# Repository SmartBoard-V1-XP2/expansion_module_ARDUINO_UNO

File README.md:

# Expansion Module: Arduino UNO

## Overview
This repository hosts the design and implementation of an expansion module that is fully compatible with Arduino UNO, utilizing a single smartboard connector. This module is specifically designed to facilitate and enhance working with FPGA systems within the smartboard ecosystem. It allows for UART connection to FPGA circuits, and I2C communication with the smartboard's socket bus, enabling easy programming and configuration of other modules requiring I2C setup. Additionally, it supports sending and receiving interrupts to/from the FPGA, streamlining high-level debugging and simplifying hardware project control loaded onto the FPGA matrix.

The module's integration with Arduino's simplicity allows for the rapid addition of software functions for debugging or configuring hardware components, such as cameras, making it an invaluable tool for accelerating and improving work with FPGA systems on smartboards. It offers an efficient way to implement high-level debugging and straightforward project control over the hardware setup.

The module is programmed via a USB port, ensuring easy and accessible firmware updates and configurations. Users are reminded to load the Arduino firmware into the module upon assembly for booting, communication, and programming purposes.

## ATmega32u4 Microcontroller

The core of this expansion module is the ATmega32u4 microcontroller, which brings the advantage of having built-in USB communication, eliminating the need for an external USB-to-serial converter. This microcontroller operates at a frequency of 16 MHz and is equipped with 32KB of flash memory, 2.5KB of SRAM, and 1KB of EEPROM. Its integrated USB functionality not only simplifies programming and communication but also enables the module to act as a USB device itself, such as a mouse, keyboard, or other HID device, opening up a plethora of possibilities for embedded projects.

Key features of the ATmega32u4 include:
- Native USB support, facilitating direct programming and communication without additional hardware.
- 23 general-purpose input/output pins (GPIO), including PWM, analog inputs, and support for I2C and SPI communication.
- Built-in hardware support for serial communication via USART, making it ideal for projects that require communication with other microcontrollers or devices.

This microcontroller's versatility and comprehensive feature set make it an excellent choice for developers looking to leverage Arduino UNO compatibility with enhanced connectivity and processing capability.

For more detailed information on the ATmega32u4 microcontroller, including technical specifications and usage guidelines, please refer to the [ATmega32u4 Datasheet](ATmega16U4-32U4-DTE.pdf) available in this repository.

## Arduino UNO Software Compatibility

This expansion module harnesses the ATmega32u4 microcontroller, ensuring software compatibility with the Arduino UNO environment. While the physical layout of the module differs from standard Arduino UNO boards, making it incompatible with Arduino shields, it retains software compatibility. This means all the digital and analog pins, UART interfaces, and other peripherals like buttons and LEDs are mapped in accordance with the Arduino UNO's configuration, facilitating seamless integration with Arduino sketches and libraries.

The module's design prioritizes integration with smartboard systems while maintaining the ease of programming and versatility associated with the Arduino software environment. Developers can utilize the familiar Arduino IDE for programming the module, taking advantage of the vast collection of libraries and tools available within the Arduino ecosystem to expedite development and prototyping processes.

Key aspects of Arduino UNO software compatibility include:
- Use of the Arduino IDE for programming, which supports direct USB programming of the ATmega32u4 without the need for an external programmer.
- Alignment with Arduino UNO's pin mapping and functionality, ensuring that existing Arduino code and libraries can be used without modification.
- Support for Arduino's standard communication protocols, allowing the module to interface with other devices and modules through UART and I2C, as well as handle interrupts, in a manner consistent with Arduino UNO projects.

This approach allows the module to blend the robust hardware capabilities of the ATmega32u4 with the user-friendly software environment of Arduino, making it ideal for a wide range of applications from educational projects to complex IoT devices.

Developers are encouraged to install the Arduino bootloader and utilize the Arduino IDE for an optimal programming experience, leveraging the compatibility to streamline development and enhance the module's functionality within the smartboard ecosystem.

## Design Documentation

Below are images showcasing various aspects of the expansion module, providing a visual overview of its design, layout, and integration capabilities:

- **Schematic Overview**
  
  This image presents the schematic diagram of the expansion module, detailing the electrical connections and components.

- **Board Design**
  
  Here is the physical layout of the PCB, showing the placement of components and the overall design of the board.

- **Module Size and Dimensions**
  
  This picture illustrates the module's dimensions and size, providing a clear view of its compactness and how it fits within a smartboard system.

- **Integration with Smartboard and Arduino UNO**
  
  A visual representation of how the module integrates with a smartboard, including an example setup featuring an Arduino UNO.

- **Smartboard System Example**
  
  An example of a smartboard system fully equipped with several expansion modules, demonstrating the modular nature and versatility of the smartboard ecosystem.

These images collectively offer a comprehensive view of the expansion module's design, functionality, and integration potential within smartboard projects.

## Contributions and Feedback
Contributions to this project are welcome. If you have suggestions for improvement or have developed additional features, please fork the repository, make your changes, and submit a pull request. For any questions or issues, please open an issue in the GitHub repository.

## License
This project is licensed under the MIT License with the following terms:

- **Permission to Use**: You are free to use, modify, and distribute this design in both private and commercial settings.
- **Attribution Requirement**: While not required, attribution to the original author, Adam Łuczak, is appreciated. This can be done through a citation or a link back to this repository.
- **No Warranty**: This design is provided "as is", without warranty of any kind. Use it at your own risk.
- **Liability**: The author is not liable for any damages or losses that may arise from the use of this design.

For the full terms and conditions, please refer to the MIT License documentation.

## Contact
Should you have any inquiries or suggestions regarding this project, please don't hesitate to contact Adam Łuczak at adam.luczak@outlook.com.

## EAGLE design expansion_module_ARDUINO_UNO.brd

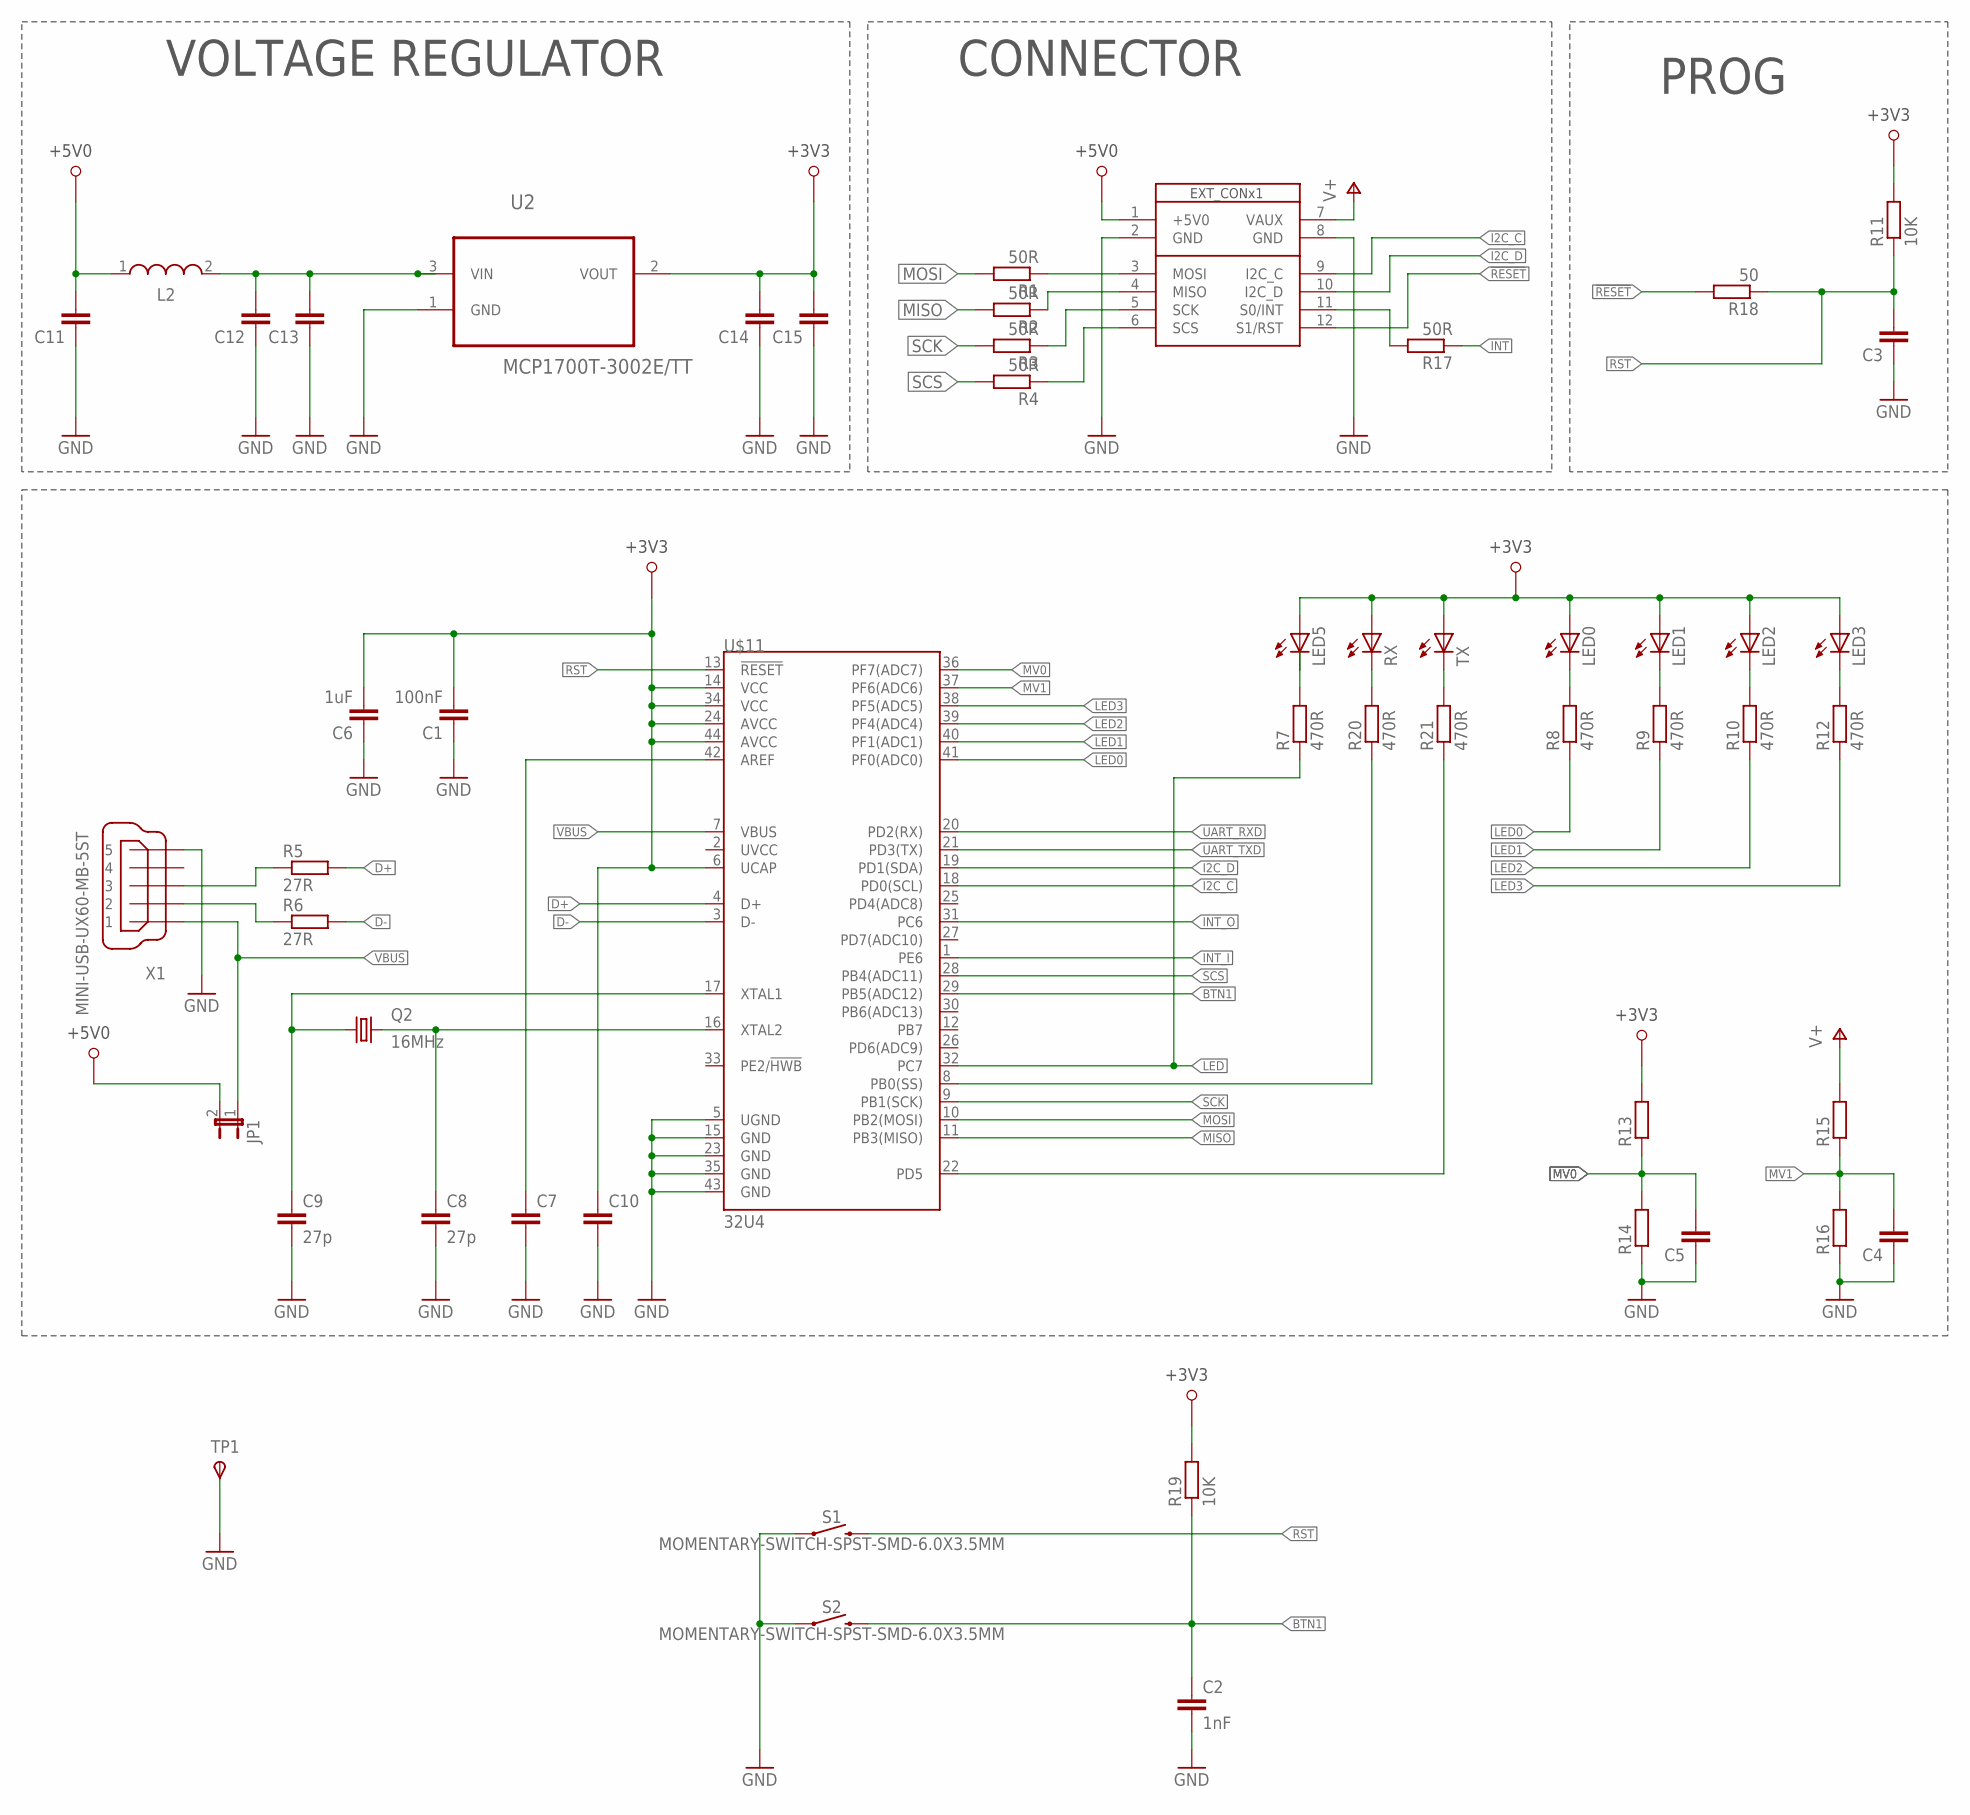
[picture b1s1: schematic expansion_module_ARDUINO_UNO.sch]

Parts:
C1: 100nF; C0603
C2: 1nF; C0603K
C3, C4, C5, C11, C12, C13, C14, C15: C-EUC0603; C0603
C6: 1uF; C0603
C7, C10: C-EUC0603K; C0603K
C8, C9: 27p; C0603K
JP1: JP1E; JP1
L2: WE-LQ_1210; WE-LQ_M
LED0, LED1, LED2, LED3, LED5: LED_ESML0603; LED_SML0603
Q2: 16MHz; 5.0X3.2_KX-9A
R1, R2, R3, R4, R17: 50R; R0603
R5, R6: 27R; R0603
R7, R8, R9, R10, R12, R20, R21: 470R; R0603
R11, R19: 10K; R0603
R13, R14, R15, R16: R-EU_R0603; R0603
R18: 50; R0603
RX: LED_ESML0603; LED_SML0603
S1, S2: MOMENTARY-SWITCH-SPST-SMD-6.0X3.5MM; TACTILE_SWITCH_SMD_6.0X3.5MM
TP1: TPSPAD1-13; P1-13
TX: LED_ESML0603; LED_SML0603
U2: MCP1700T-3002E/TT; SOT95P237X112-3N
U$1: SB_EXT_CON_X1_SPI; SB_EXT_CON_X1_FULL
U$11: 32U4; TQFP44
X1: MINI-USB-UX60-MB-5ST; UX60-MB-5ST

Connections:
!RESET: R18.2, U$1.12 (S1/RST)
+3V3: C1.2, C6.2, C10.1, C14.2, C15.2, LED0.A, LED1.A, LED2.A, LED3.A, LED5.A, R11.2, R13.2, R19.2, RX.A, TX.A, U2.2 (VOUT), U$11.6 (UCAP), U$11.14 (VCC), U$11.24 (AVCC), U$11.34 (VCC), U$11.44 (AVCC)
+5V0: C11.2, JP1.2, L2.1, U$1.1 (+5V0)
BTN1: C2.1, R19.1, S2.2, U$11.29 (PB5(ADC12))
D+: R5.2, U$11.4 (D+)
D-: R6.2, U$11.3 (D-)
GND: C1.1, C2.2, C3.1, C4.1, C5.1, C6.1, C7.2, C8.2, C9.2, C10.2, C11.1, C12.1, C13.1, C14.1, C15.1, R14.1, R16.1, S1.1, S2.1, TP1.TP, U2.1 (GND), U$1.2 (GND), U$1.8 (GND), U$11.5 (UGND), U$11.15 (GND), U$11.23 (GND), U$11.35 (GND), U$11.43 (GND), X1.5
I2C_C: U$1.9 (I2C_C), U$11.18 (PD0(SCL))
I2C_D: U$1.10 (I2C_D), U$11.19 (PD1(SDA))
INT: R17.1
INT_I: U$11.1 (PE6)
INT_O: U$11.31 (PC6)
LED: R7.1, U$11.32 (PC7)
LED0: R8.1, U$11.41 (PF0(ADC0))
LED1: R9.1, U$11.40 (PF1(ADC1))
LED2: R10.1, U$11.39 (PF4(ADC4))
LED3: R12.1, U$11.38 (PF5(ADC5))
MISO: R2.2, U$11.11 (PB3(MISO))
MOSI: R1.2, U$11.10 (PB2(MOSI))
MV0: C5.2, R13.1, R14.2, U$11.36 (PF7(ADC7))
MV1: C4.2, R15.1, R16.2, U$11.37 (PF6(ADC6))
unnamed: R1.1, U$1.3 (MOSI)
unnamed: R2.1, U$1.4 (MISO)
unnamed: R3.1, U$1.5 (SCK)
unnamed: R4.1, U$1.6 (SCS)
unnamed: LED5.C, R7.2
unnamed: C7.1, U$11.42 (AREF)
unnamed: R20.1, U$11.8 (PB0(SS))
unnamed: C9.1, Q2.1, U$11.17 (XTAL1)
unnamed: C8.1, Q2.3 (2), U$11.16 (XTAL2)
unnamed: LED0.C, R8.2
unnamed: LED1.C, R9.2
unnamed: R6.1, X1.2
unnamed: R5.1, X1.3
unnamed: LED2.C, R10.2
unnamed: LED3.C, R12.2
unnamed: R21.1, U$11.22 (PD5)
unnamed: R21.2, TX.C
unnamed: R20.2, RX.C
unnamed: C12.2, C13.2, L2.2, U2.3 (VIN)
unnamed: R17.2, U$1.11 (S0/INT)
RST: C3.2, R11.1, R18.1, S1.2, U$11.13 (!RESET)
SCK: R3.2, U$11.9 (PB1(SCK))
SCS: R4.2, U$11.28 (PB4(ADC11))
UART_RXD: U$11.20 (PD2(RX))
UART_TXD: U$11.21 (PD3(TX))
V+: R15.2, U$1.7 (VAUX)
VBUS: JP1.1, U$11.7 (VBUS), X1.1

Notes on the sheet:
CONNECTOR
VOLTAGE REGULATOR
PROG

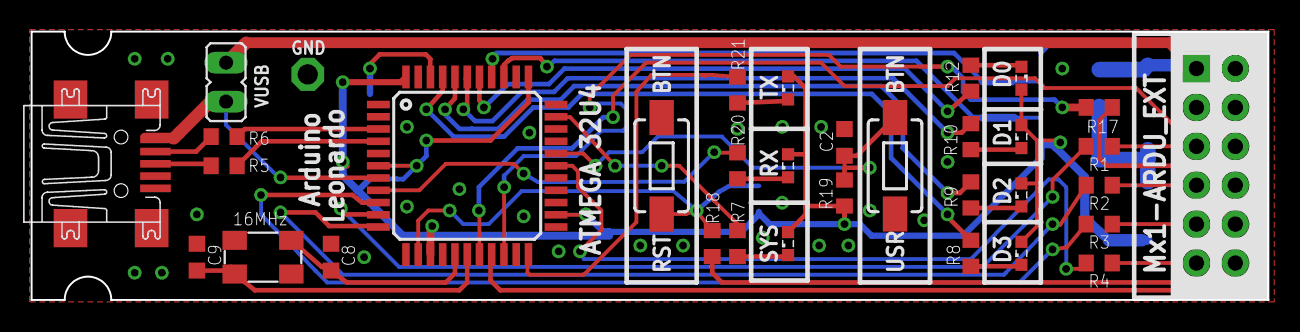
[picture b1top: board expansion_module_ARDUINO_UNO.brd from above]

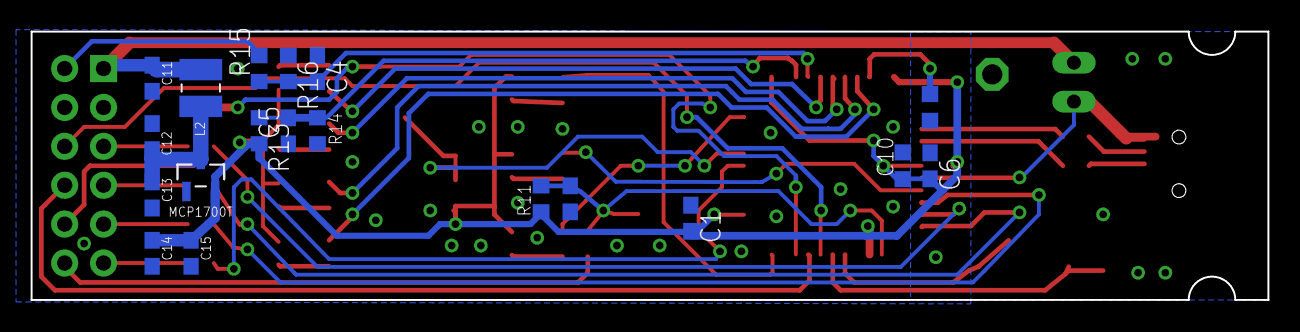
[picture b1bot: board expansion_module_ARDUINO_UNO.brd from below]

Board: 2 copper layers, 80.8 x 17.5 mm, 53 parts (19 on the bottom side), 43 nets.

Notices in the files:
README.md:
License: MIT
parts and their libraries:
SparkFun-IC-Microcontroller: Licensing: Creative Commons ShareAlike 4.0 International - https://creativecommons.org/licenses/by-sa/4.0
EagleLibrary_Wuerth_Elektronik_eiSos_rev: Copyright: Würth Elektronik
crystal-geyer_V1_0: Copyright: Geyer-Electronic
